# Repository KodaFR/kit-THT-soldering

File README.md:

# Kit THT Soldering

<p align="center">
  Un kit électronique à assembler et à programmer autour d’un <strong>ESP32-S3</strong>.<br>
  🔧 Assemblez la carte · 💻 Téléversez le firmware · 🎮 Explorez son interface
</p>

## 🧭 Parcours

```mermaid
flowchart LR
    A["🧰 Préparer le matériel"] --> B["🔥 Souder selon la BOM<br/>et la sérigraphie"]
    B --> C["🔌 Brancher en USB-C"]
    C --> D["⚙️ Configurer Arduino IDE"]
    D --> E["⬆️ Téléverser le firmware"]
    E --> F["🎮 Utiliser les boutons et l'écran"]
```

<details>
<summary>Afficher le sommaire</summary>

- [🧰 Avant de commencer](#avant-de-commencer)
- [🔥 1. Assembler la carte](#assembler-la-carte)
- [⚙️ 2. Installer Arduino IDE](#installer-arduino-ide)
- [⬆️ 3. Téléverser le firmware](#televerser-le-firmware)
- [🎮 4. Utiliser la carte](#utiliser-la-carte)
- [📖 Guide de jeu](#guide-de-jeu)
- [🛠️ Dépannage](#depannage)
- [📂 Fichiers du projet](#fichiers-du-projet)

</details>

## 🧰 Avant de commencer

### 🧪 Matériel

- Le circuit imprimé et les composants indiqués dans la [BOM](kitkodatht.csv).
- Un fer à souder et de l’étain à souder.
- Un câble **USB-C capable de transférer des données** (certains câbles ne servent qu’à la charge).
- Un ordinateur avec Arduino IDE.

| Indispensable | Pratique, mais facultatif |
| --- | --- |
| 🔥 Fer à souder | 🧵 Tresse à dessouder |
| 🧴 Étain à souder | ✨ Flux de soudure |
| 🔌 Câble USB-C avec données | |
| 💻 Ordinateur avec Arduino IDE | |

La tresse à dessouder et le flux peuvent être utiles pour corriger une soudure
ou faciliter le travail, mais ils ne sont pas nécessaires pour assembler le kit.

### 🔎 Repérer les composants

Vérifiez la [BOM à la racine du dépôt](kitkodatht.csv) avant de commencer.
La sérigraphie imprimée sur le PCB indique où placer les composants et leurs
repères (`R1`, `SW1`, etc.). Respectez les valeurs et le sens des composants
polarisés indiqués par la BOM et la sérigraphie.

## 🔥 1. Assembler la carte

> ⚠️ **Sécurité :** ne branchez pas la carte à l’USB pendant la soudure.

1. **📋 Triez** les composants et comparez-les à la [BOM](kitkodatht.csv).
2. **🔎 Repérez** les emplacements grâce aux références sur le PCB. Vérifiez la
   valeur des résistances et l’orientation des composants polarisés.
3. **🔥 Soudez** les composants traversants selon leur contour sur la
   sérigraphie. Pour les composants à plusieurs broches, alignez-les avant de
   souder toutes les broches.
4. **✂️ Nettoyez et inspectez** : coupez les pattes qui dépassent et vérifiez
   qu’il n’y a ni pont d’étain ni broche dessoudée.
5. **✅ Contrôlez** l’absence de débris ou d’excès d’étain pouvant provoquer un
   court-circuit.

> 💡 Le **module ESP32-S3 DevKitC** se connecte au PCB et se programme par son
> port USB-C. Une fois la soudure terminée et inspectée, branchez-le en USB-C
> pour configurer Arduino IDE et téléverser le firmware.

## ⚙️ 2. Installer Arduino IDE

1. Téléchargez et installez [Arduino IDE](https://www.arduino.cc/en/software).
2. **Ajoutez le support de l’ESP32** :
   - Ouvrez **Fichier → Préférences** (Windows/Linux) ou
     **Arduino IDE → Settings/Preferences** (macOS).
   - Dans **URL de gestionnaire de cartes supplémentaires**, ajoutez :
     `https://espressif.github.io/arduino-esp32/package_esp32_index.json`
   - Ouvrez **Outils → Type de carte → Gestionnaire de cartes**, recherchez
     **esp32** et installez **esp32 by Espressif Systems**.
3. **Installez les bibliothèques** depuis **Outils → Gérer les bibliothèques**.
   Recherchez puis installez chacune des bibliothèques indiquées dans
   [`requirements.txt`](requirements.txt) :
   - **Adafruit GFX Library**
   - **Adafruit SH110X**
   - **Adafruit BusIO**

## ⬆️ 3. Téléverser le firmware

1. 🔌 Branchez le module ESP32-S3 au PC avec un câble USB-C de données. Si le
   module est amovible, installez-le sur le PCB avant de le connecter.
2. 📄 Dans Arduino IDE, ouvrez le sketch
   [`firmware/main/main.ino`](firmware/main/main.ino).
3. 🎛️ Dans **Outils → Type de carte**, sélectionnez **ESP32S3 Dev Module**.
   Selon la version du paquet ESP32, **ESP32-S3-DevKitC-1** peut aussi être
   proposé.
4. 🔗 Dans **Outils → Port**, choisissez le port série apparu lors du
   branchement de la carte.
5. ✅ Cliquez sur **Vérifier** pour compiler, puis sur **Téléverser** pour
   envoyer le programme.
   - Si le téléversement reste bloqué sur la connexion, maintenez **BOOT** sur
     le module, lancez le téléversement, puis relâchez BOOT quand la connexion
     commence.
6. 🖥️ Ouvrez le **Moniteur série** et sélectionnez **9600 bauds** pour lire
   les messages de démarrage.

## 🎮 4. Utiliser la carte

Au démarrage, l’écran affiche l’accueil et le buzzer joue une mélodie. Utilisez
les boutons de la carte :

| Bouton | Action |
| --- | --- |
| ⏺️ **Central** | Appui court : sélectionner ou effectuer une action. Appui long : revenir au menu. |
| ◀️ **Gauche** | Parcourir le menu vers la gauche ; dans **Jouer**, jouer à gauche. |
| ▶️ **Droit** | Parcourir le menu vers la droite ; dans **Jouer**, jouer à droite. |

🥚 **Pour commencer :** appuyez au centre pour quitter l’accueil, puis appuyez
quatre fois au centre pour faire éclore l’œuf. Utilisez ensuite gauche et droite
pour parcourir le menu. Un appui court au centre ouvre l’écran sélectionné ;
un appui long au centre revient au menu depuis une activité ou un écran de
statistiques.

## 📖 Guide de jeu

### Comprendre les boutons

| Commande | Action |
| --- | --- |
| ◀️ Gauche / ▶️ Droit dans le menu | Parcourir les pages du menu. |
| ⏺️ Appui court au centre | Ouvrir une page, effectuer une action ou fermer une fenêtre. |
| ⏺️ Appui long au centre | Revenir au menu depuis une activité ou les statistiques. |
| ◀️ + ▶️ dans **Jouer** | Jouer du côté gauche, du côté droit ou des deux côtés simultanément. |

### Activités et récompenses

- **Apprendre :** après une seconde, une anecdote éducative apparaît. Un appui
  court la ferme ; l’appui suivant affiche une autre anecdote. Chaque appui
  dans cette activité compte comme une leçon : environ **5 leçons** donnent
  **1 point de culture** et chaque leçon rapporte **2 pièces**.
- **Jouer :** appuyez sur gauche, droite ou les deux boutons latéraux. Chaque
  action compte comme une partie ; environ **50 parties** donnent **1 point de
  bonheur**.
- **Expérimenter :** l’activité lance une recherche des réseaux Wi-Fi proches.
  La fenêtre de résultat indique les réseaux trouvés et la créativité gagnée.
  Chaque réseau contribue à la créativité ; le talent du compagnon peut faire
  varier légèrement la progression. Chaque tranche de **4 réseaux trouvés dans
  une recherche** rapporte **1 pièce**. Fermez le résultat avec le bouton
  central ; un nouvel appui lance une autre recherche.
- **Nourrir :** un repas coûte **15 pièces**. Appuyez trois fois au centre pour
  manger la pomme ; le compagnon gagne jusqu’à **3 points de faim**, sans
  dépasser le maximum de **5**. Le résultat indique le gain réel. Un compagnon
  déjà rassasié ne peut pas manger.

Les talents sont légèrement aléatoires : les seuils de culture et de bonheur
peuvent donc varier de quelques actions d’un compagnon à l’autre.

### Argent, faim et santé

- Le moyen le plus régulier de gagner de l’argent est **Apprendre** :
  **2 pièces par leçon**. L’expérimentation peut aussi rapporter une pièce par
  tranche de quatre réseaux trouvés pendant une recherche.
- La faim commence à **5** et baisse d’un point toutes les **5 minutes**. Le
  compagnon prend également un an toutes les 5 minutes.
- La santé est comprise entre **0 et 5**. Si la faim vaut **0**, la santé baisse
  d’un point toutes les 5 minutes. Si la faim vaut **5** au moment d’une mise à
  jour, la santé remonte d’un point ; avec toute autre valeur, elle ne change
  pas.
- À **0 santé**, le compagnon meurt. La mélodie de défaite est jouée, puis une
  nouvelle partie commence avec un nouvel œuf.

### Code secret

Sur la page **Animal** du menu, appuyez simultanément sur les trois boutons
(gauche, centre et droit) pour tuer instantanément le compagnon. La mélodie de
défaite joue, puis le jeu recommence avec un nouvel œuf.

## 🛠️ Dépannage

- 🔌 **La carte n’apparaît pas dans la liste des ports :** essayez un autre câble
  USB-C (avec données), un autre port USB ou installez le pilote USB adapté à
  votre module.
- ⬆️ **Le téléversement ne démarre pas :** vérifiez la carte et le port
  sélectionnés, puis essayez la procédure avec le bouton BOOT décrite plus haut.
- 📚 **La compilation échoue sur une bibliothèque :** installez ou mettez à jour
  les trois bibliothèques Adafruit indiquées dans
  [`requirements.txt`](requirements.txt).
- 🖥️ **L’écran reste vide ou un composant ne répond pas :** débranchez l’USB,
  vérifiez la BOM, l’orientation et les soudures, puis rebranchez la carte.
- 📟 **Le moniteur série affiche des caractères illisibles :** sélectionnez
  **9600 bauds**.

## 📂 Fichiers du projet

- [`kitkodatht/`](kitkodatht/) — schéma, PCB et projet KiCad.
- [`kitkodatht.csv`](kitkodatht.csv) — BOM de référence du kit.
- [`firmware/main/`](firmware/main/) — firmware Arduino.
- [`visuels/pcb.png`](visuels/pcb.png) — aperçu du PCB.

---

<p align="center">
  <strong>🧡 Bon assemblage et bon amusement !</strong><br>
  Un doute ? Vérifiez d’abord la BOM et la sérigraphie avant de mettre la carte sous tension.
</p>

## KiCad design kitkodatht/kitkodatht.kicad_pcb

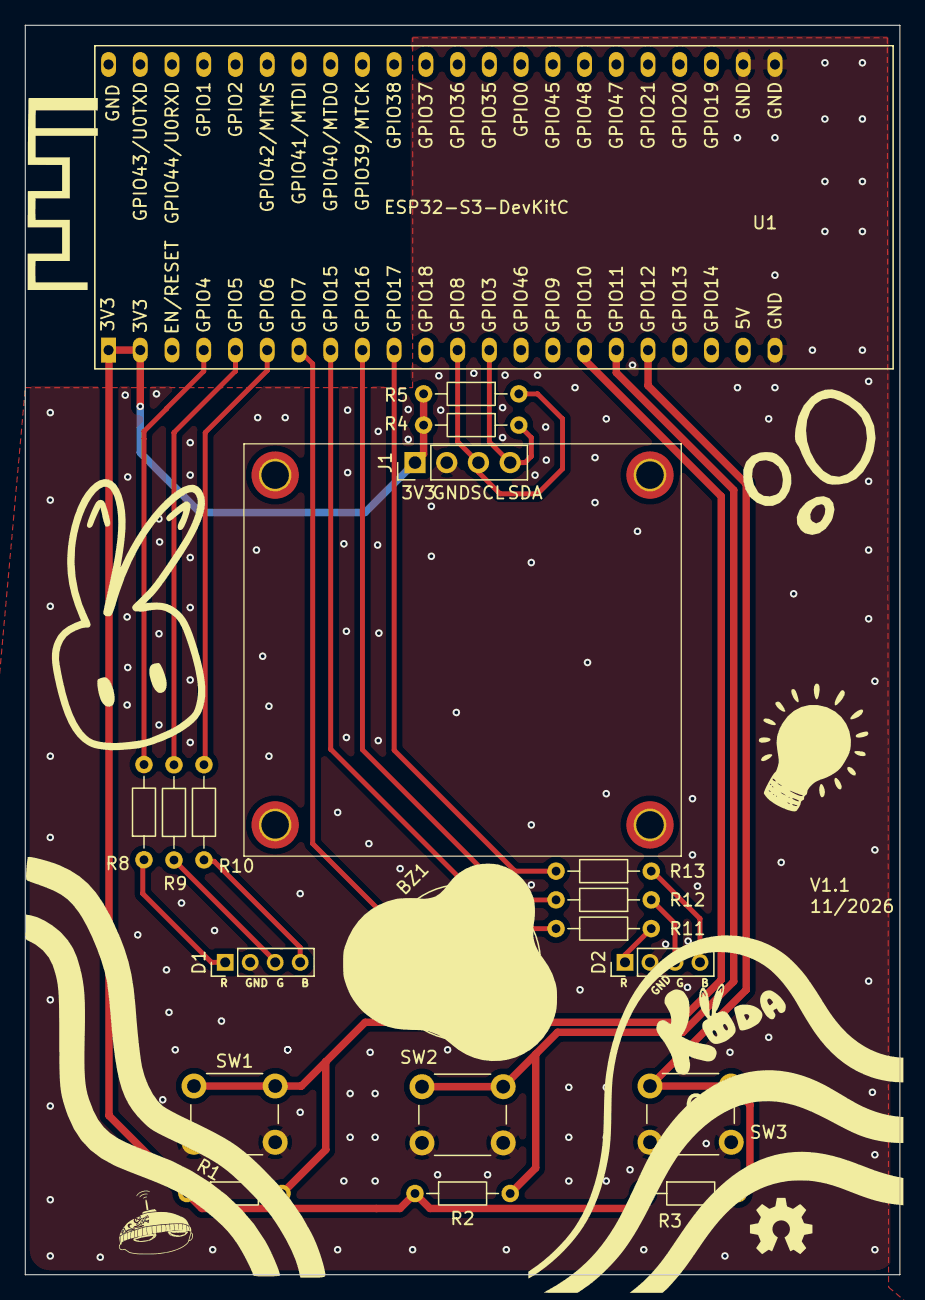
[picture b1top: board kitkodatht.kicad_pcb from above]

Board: 2 copper layers, 70.0 x 100.0 mm, 19 parts (0 on the bottom side), 20 nets.

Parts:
BZ1: Buzzer; Buzzer_TDK_PS1240P02BT_D12.2mm_H6.5mm
D1, D2: LED_KRGB; PinHeader_1x04_P2.00mm_Vertical
J1: Conn_01x04_Pin; PinHeader_1x04_P2.54mm_Vertical
R1, R2, R3, R4, R5: 10k; R_Axial_DIN0204_L3.6mm_D1.6mm_P7.62mm_Horizontal
R8, R9, R10, R11, R12, R13: R_Axial_DIN0204_L3.6mm_D1.6mm_P7.62mm_Horizontal
SW1, SW2, SW3: SW_Push; SW_PUSH_6mm
U1: ESP32-S3-DevKitC

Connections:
+3V3: J1.1, R1.1, R2.1, R3.1, R4.1, R5.1, U1.1 (3V3), U1.2 (3V3)
/BTN_LEFT: R1.2, SW1.1, U1.16 (GPIO10/ADC1_CH9)
/BTN_RIGHT: R3.2, SW3.1, U1.18 (GPIO12/ADC2_CH1)
/BTN_SELECT: R2.2, SW2.1, U1.17 (GPIO11/ADC2_CH0)
/BUZZER: BZ1.1 (+), U1.7 (GPIO7/ADC1_CH6)
/LEFT_LED_B: R10.2, U1.6 (GPIO6/ADC1_CH5)
/LEFT_LED_G: R9.2, U1.5 (GPIO5/ADC1_CH4)
/LEFT_LED_R: R8.2, U1.4 (GPIO4/ADC1_CH3)
/RIGHT_LED_B: R13.2, U1.10 (GPIO17/ADC2_CH6)
/RIGHT_LED_G: R12.2, U1.9 (GPIO16/ADC2_CH5/32K_N)
/RIGHT_LED_R: R11.2, U1.8 (GPIO15/ADC2_CH4/32K_P)
/SCL: J1.3, R5.2, U1.12 (GPIO8/ADC1_CH7)
/SDA: J1.4, R4.2, U1.13 (GPIO3/ADC1_CH2)
GND: BZ1.2 (-), D1.2 (K), D2.2 (K), J1.2, SW1.2, SW2.2, SW3.2, U1.22 (GND), U1.23 (GND), U1.24 (GND), U1.44 (GND)
unnamed: D1.4 (BA), R10.1
unnamed: D1.3 (GA), R9.1
unnamed: D1.1 (RA), R8.1
unnamed: D2.4 (BA), R13.1
unnamed: D2.3 (GA), R12.1
unnamed: D2.1 (RA), R11.1

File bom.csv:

"Reference","Qty","Value","DNP","Exclude from BOM","Exclude from Board","Footprint","Datasheet"
"BZ1","1","Buzzer","","","","Buzzer_Beeper:Buzzer_TDK_PS1240P02BT_D12.2mm_H6.5mm",""
"D1,D2","2","LED_KRGB","","","","Connector_PinHeader_2.00mm:PinHeader_1x04_P2.00mm_Vertical",""
"J1","1","Conn_01x04_Pin","","","","Connector_PinHeader_2.54mm:PinHeader_1x04_P2.54mm_Vertical",""
"R1,R2,R3,R4,R5","5","10k","","","","Resistor_THT:R_Axial_DIN0204_L3.6mm_D1.6mm_P7.62mm_Horizontal",""
"R8,R9,R10,R11,R12,R13","6","","","","","Resistor_THT:R_Axial_DIN0204_L3.6mm_D1.6mm_P7.62mm_Horizontal",""
"SW1,SW2,SW3","3","SW_Push","","","","Button_Switch_THT:SW_PUSH_6mm",""
"U1","1","ESP32-S3-DevKitC","","","","myfootprints:ESP32-S3-DevKitC",""

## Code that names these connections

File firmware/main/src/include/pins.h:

#define SDA_PIN 3
#define SCL_PIN 8
#define OLED_RESET -1

#define BTN_LEFT 10
#define BTN_RIGHT 12
#define BTN_SELECT 11

#define BUZZER 7

#define PINLEFT_R 4
#define PINLEFT_G 5
#define PINLEFT_B 6

#define PINRIGHT_R 15
#define PINRIGHT_G 16
#define PINRIGHT_B 17
